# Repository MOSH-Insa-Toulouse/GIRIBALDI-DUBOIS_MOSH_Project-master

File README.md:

# MOSH_Project: Connected gas Sensor
> GIRIBALDI Romain & DUBOIS Remy

The goal of this project is to build a **connected gas sensor** and build the interface around the sensor.

For this we use an **Arduino Uno** board and connected to it a **RN2483** chip. This chip allows us to send and receive messages from the **LoRa Network**, that we will be able to get on **The Things Network**.

First we build the code to detect gas from the sensor on the Arduino IDE, then we develop an arduino shield that can be pluged on the **Arduino Uno** board, and also the gaz sensor and the **RN2483** chip.

# Hardware Components

- **Arduino Uno** board
- **LT1050** Operational Amplifier 
- **RN2483** Microchip
- **MQ-9 groove Gas Sensor**
- A homemade sensor that will be made later at A.I.M.E.

# Arduino Code 

For the Arduino code we use the **Arduino IDE**, the goal was to detect a threshold exceeded on the gas sensor, first we do our tests with the groove gas sensor but in the end the goal is to use the homemade one. 

The source code is available on the Arduino directory.

## Kicad project
### Overview

The PCB is composed of: 
- **RN2483** chip
- Amplification stage with a **LT1050**
- **TO5** housing for the gas sensor to be created

### Schematic

### PCB Layout

### 3D Visualization

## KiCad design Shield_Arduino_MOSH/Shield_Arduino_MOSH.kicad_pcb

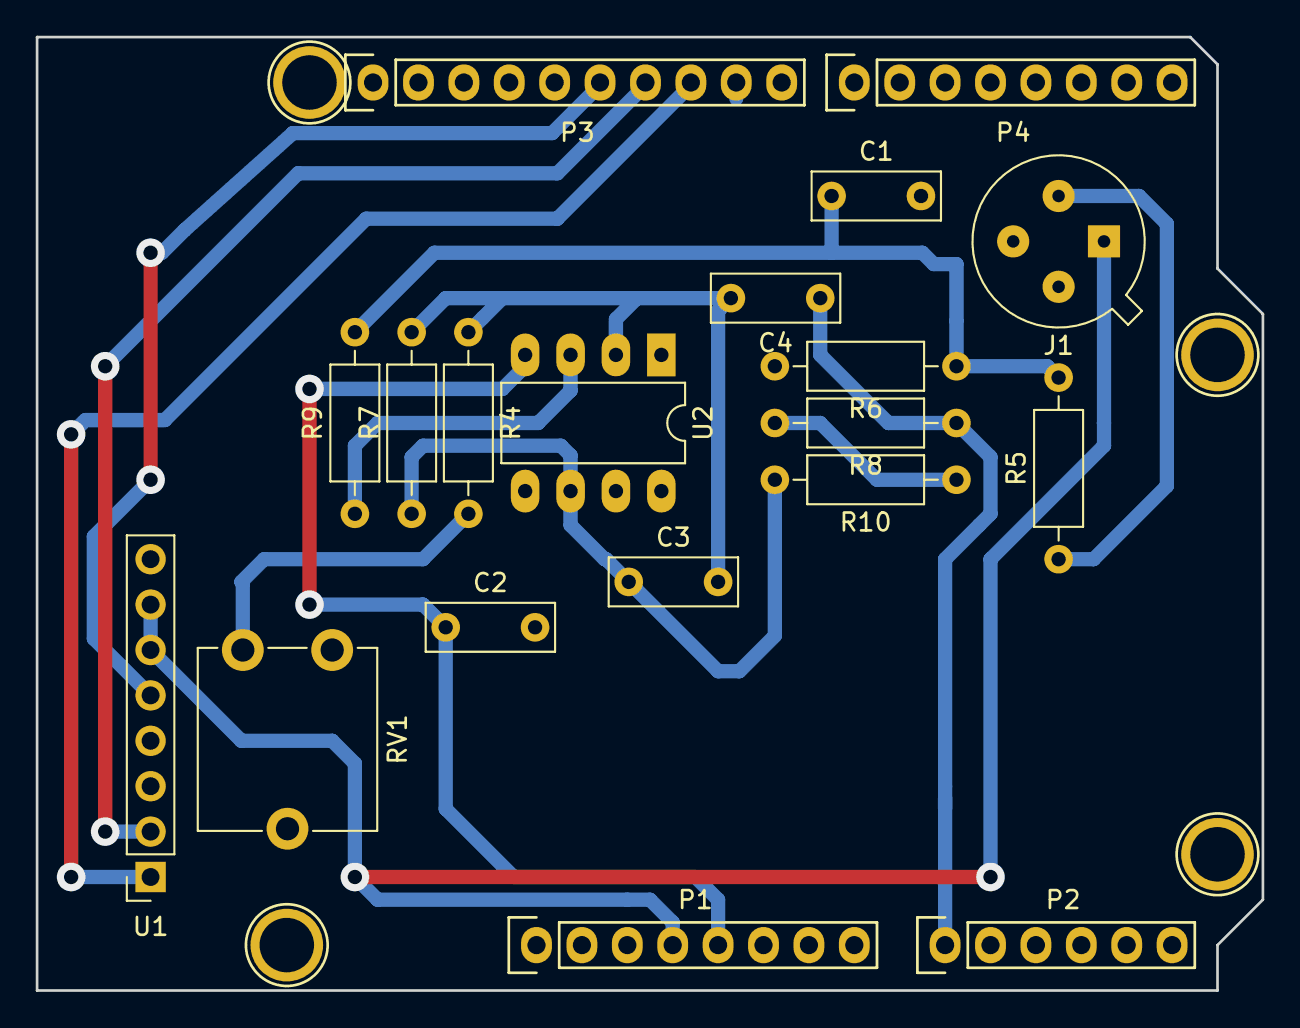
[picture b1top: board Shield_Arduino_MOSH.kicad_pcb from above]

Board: 2 copper layers, 68.6 x 53.3 mm, 23 parts (0 on the bottom side), 16 nets.

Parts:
C1, C2, C4: 100n; C_Rect_L7.0mm_W2.5mm_P5.00mm
C3: 1u; C_Rect_L7.0mm_W2.5mm_P5.00mm
J1: Conn_01x04; TO-5-4
P1: Power; Socket_Strip_Arduino_1x08
P2: Analog; Socket_Strip_Arduino_1x06
P3: Digital; Socket_Strip_Arduino_1x10
P4: Digital; Socket_Strip_Arduino_1x08
P5, P6, P7, P8: CONN_01X01; Arduino_1pin
R4: 100; R_Axial_DIN0207_L6.3mm_D2.5mm_P10.16mm_Horizontal
R5: 10k; R_Axial_DIN0207_L6.3mm_D2.5mm_P10.16mm_Horizontal
R6, R7: 100k; R_Axial_DIN0207_L6.3mm_D2.5mm_P10.16mm_Horizontal
R8: 1k; R_Axial_DIN0207_L6.3mm_D2.5mm_P10.16mm_Horizontal
R9, R10: 0; R_Axial_DIN0207_L6.3mm_D2.5mm_P10.16mm_Horizontal
RV1: 1k; Potentiometer_ACP_CA9-V10_Vertical
U1: RN2483A; PinSocket_1x08_P2.54mm_Vertical
U2: LTC1050; DIP-8_W7.62mm_LongPads

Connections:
+3V3: J1.1, P1.4, U1.6, U1.7
+5V: C2.1, P1.5, U2.4
/10(**/SS): P3.8, U1.1
/11(**/MOSI): P3.7, U1.2
/12(MISO): P3.6, U1.5
/A0: C4.1, P2.1, R8.1
/A4(SDA): P2.5, P3.2
/A5(SCL): P2.6, P3.1
/Capt_preamp: J1.2, R5.1
GND: C1.2, C2.2, J1.3, P1.6, P1.7, P3.4, R6.2, RV1.2, RV1.3, U1.8, U2.7
unnamed: C1.1, R5.2, R6.1, R9.2
unnamed: C3.1, R7.1, R10.2, U2.6
unnamed: C3.2, C4.2, R4.1, R7.2, U2.2
unnamed: R4.2, RV1.1
unnamed: R9.1, U2.3
unnamed: R8.2, R10.1
